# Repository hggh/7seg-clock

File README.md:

# seven segment clock with ambilight

 * 58x WS2812b 
 * ESP32
 * 74AHC125
 * XC6220 3.0V

To control the WS2812b LEDs the clock controller from wood clock light is used: https://github.com/hggh/wood-clock-light/tree/master/pcb/esp32-clock-base

### the base pcb for all ws2812b

### ESP32 to control all LEDs

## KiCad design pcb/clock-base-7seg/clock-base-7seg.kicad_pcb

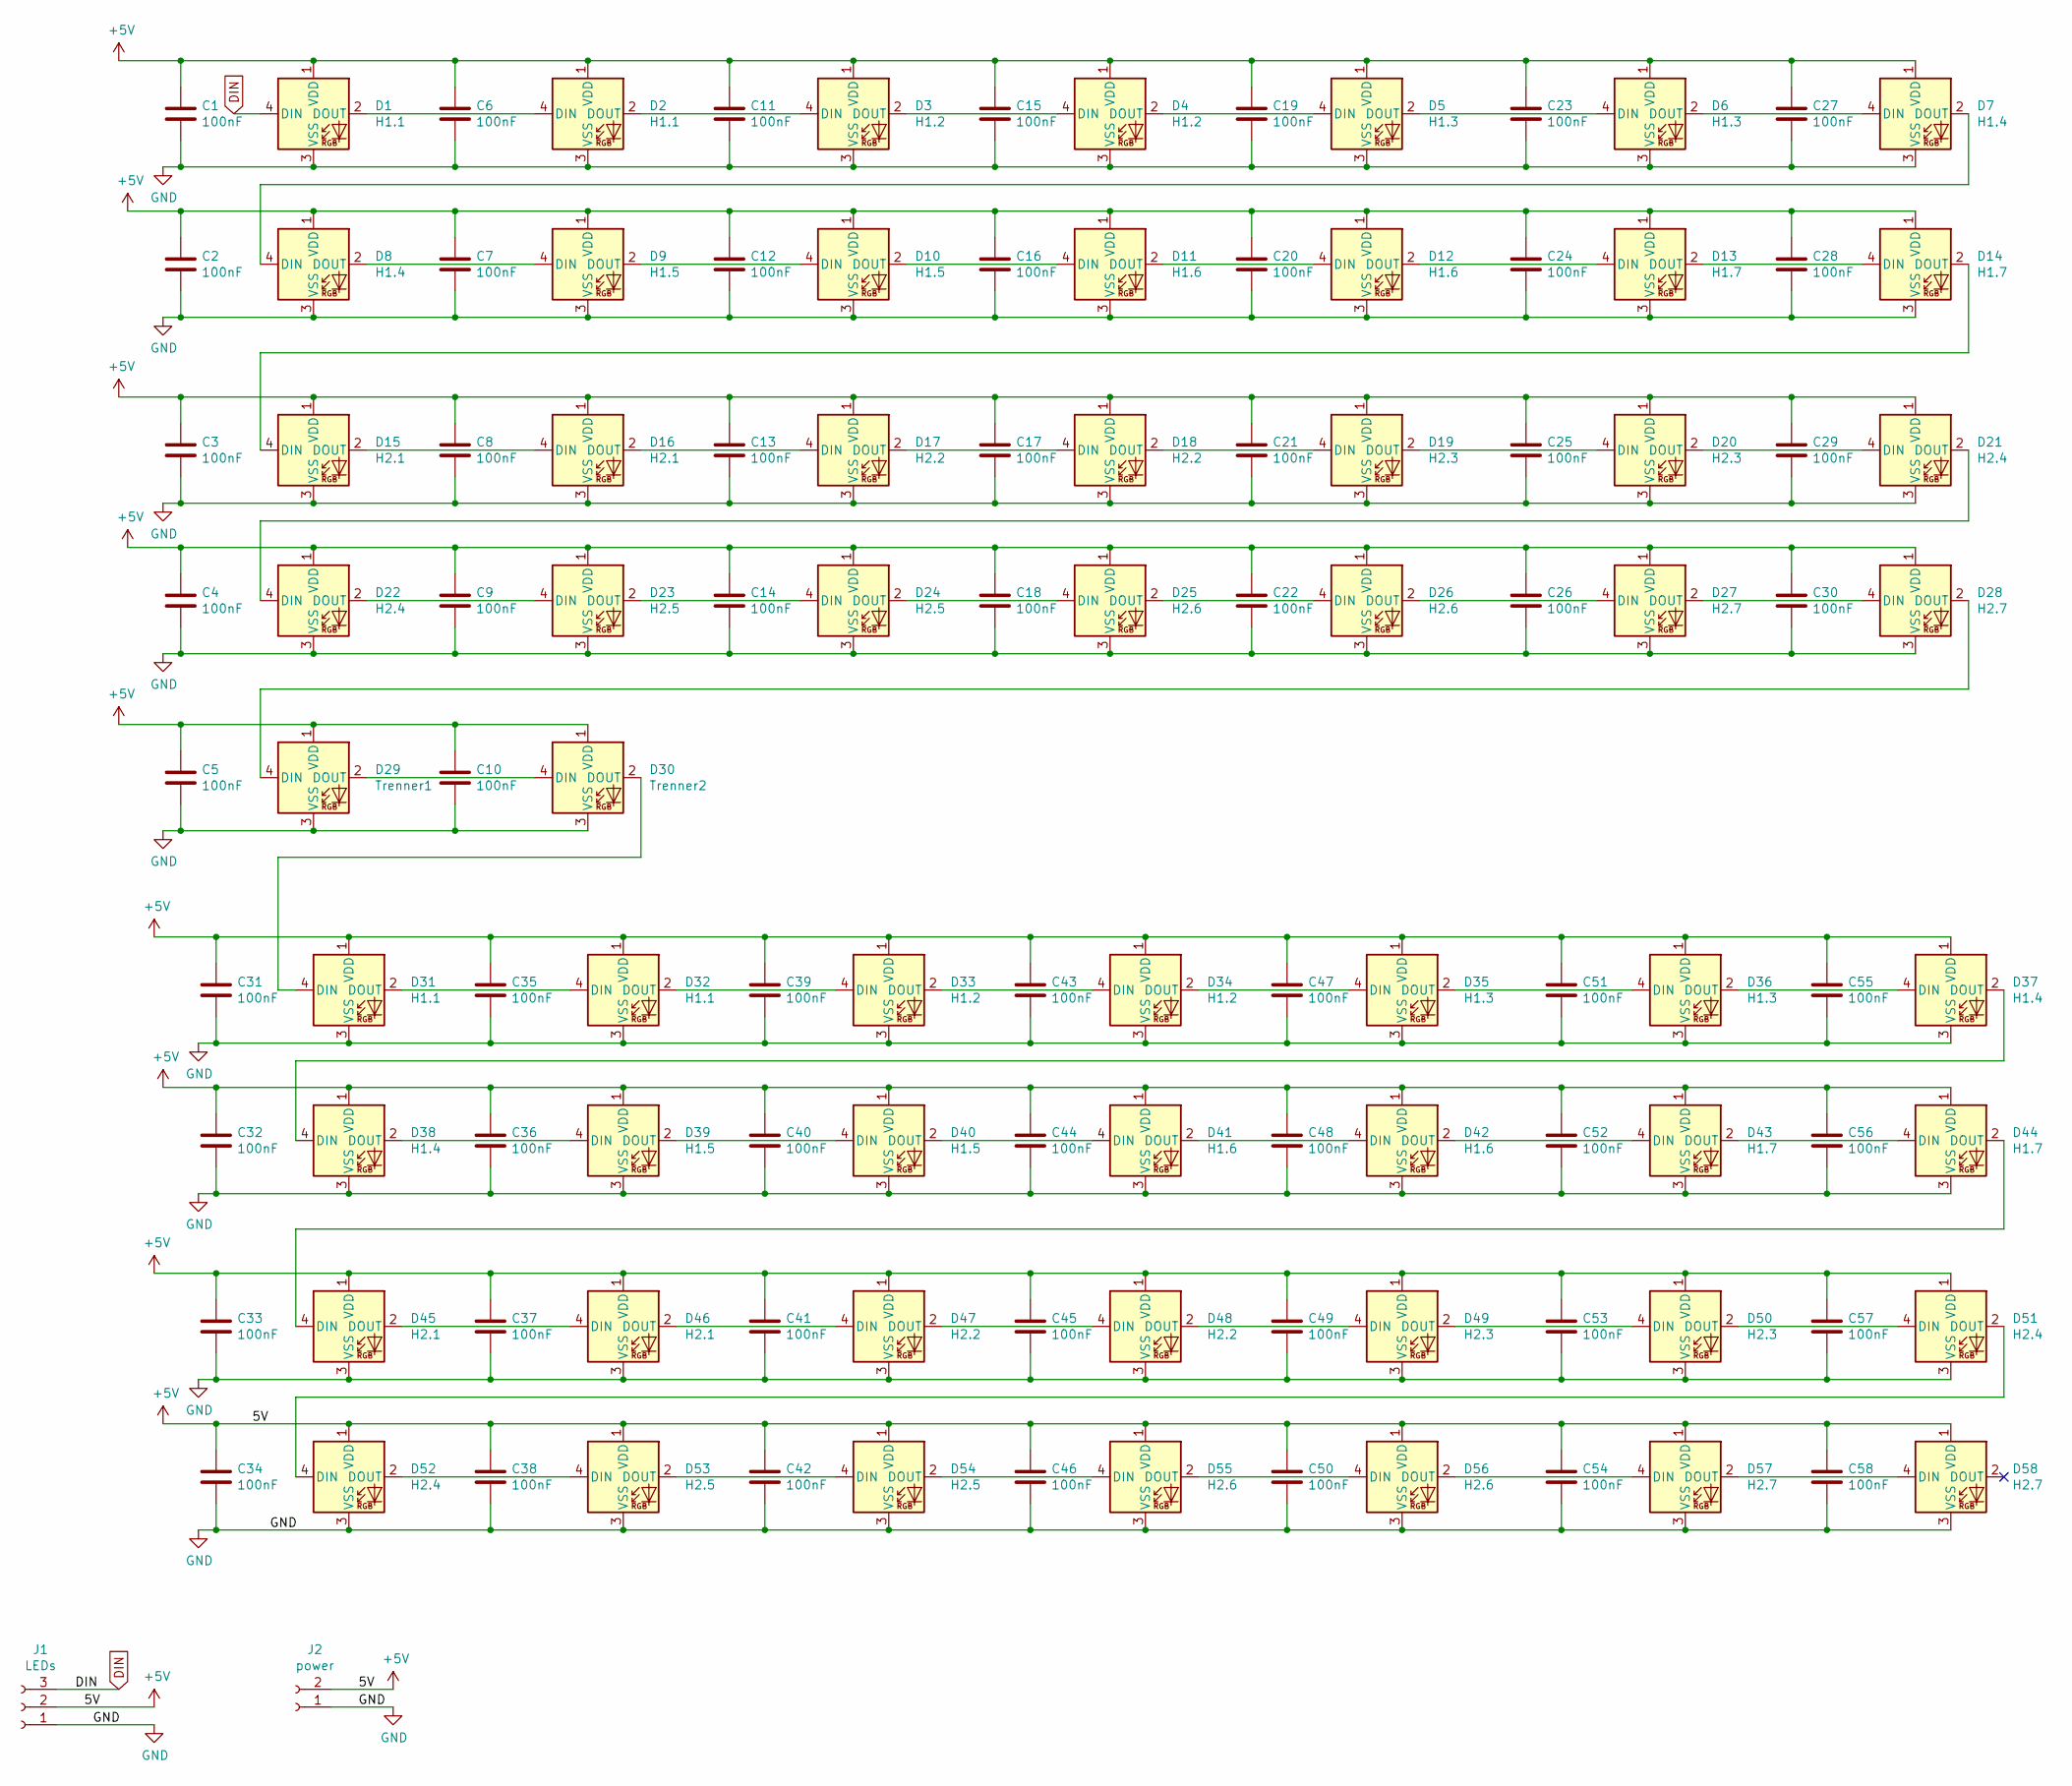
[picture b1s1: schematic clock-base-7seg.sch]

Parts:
C1, C2, C3, C4, C5, C6, C7, C8, C9, C10, C11, C12, C13, C14, C15, C16, C17, C18, C19, C20, C21, C22, C23, C24, C25, C26, C27, C28, C29, C30, C31, C32, C33, C34, C35, C36, C37, C38, C39, C40, C41, C42, C43, C44, C45, C46, C47, C48, C49, C50, C51, C52, C53, C54, C55, C56, C57, C58: 100nF; C_0805_2012Metric_Pad1.18x1.45mm_HandSolder
D1, D2, D31, D32: H1.1; LED_WS2812B_PLCC4_5.0x5.0mm_P3.2mm
D3, D4, D33, D34: H1.2; LED_WS2812B_PLCC4_5.0x5.0mm_P3.2mm
D5, D6, D35, D36: H1.3; LED_WS2812B_PLCC4_5.0x5.0mm_P3.2mm
D7, D8, D37, D38: H1.4; LED_WS2812B_PLCC4_5.0x5.0mm_P3.2mm
D9, D10, D39, D40: H1.5; LED_WS2812B_PLCC4_5.0x5.0mm_P3.2mm
D11, D12, D41, D42: H1.6; LED_WS2812B_PLCC4_5.0x5.0mm_P3.2mm
D13, D14, D43, D44: H1.7; LED_WS2812B_PLCC4_5.0x5.0mm_P3.2mm
D15, D16, D45, D46: H2.1; LED_WS2812B_PLCC4_5.0x5.0mm_P3.2mm
D17, D18, D47, D48: H2.2; LED_WS2812B_PLCC4_5.0x5.0mm_P3.2mm
D19, D20, D49, D50: H2.3; LED_WS2812B_PLCC4_5.0x5.0mm_P3.2mm
D21, D22, D51, D52: H2.4; LED_WS2812B_PLCC4_5.0x5.0mm_P3.2mm
D23, D24, D53, D54: H2.5; LED_WS2812B_PLCC4_5.0x5.0mm_P3.2mm
D25, D26, D55, D56: H2.6; LED_WS2812B_PLCC4_5.0x5.0mm_P3.2mm
D27, D28, D57, D58: H2.7; LED_WS2812B_PLCC4_5.0x5.0mm_P3.2mm
D29: Trenner1; LED_WS2812B_PLCC4_5.0x5.0mm_P3.2mm
D30: Trenner2; LED_WS2812B_PLCC4_5.0x5.0mm_P3.2mm
J1: LEDs; PinHeader_1x03_P2.54mm_Vertical
J2: power; PinHeader_1x02_P2.54mm_Vertical

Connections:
+5V: C1.1, C2.1, C3.1, C4.1, C5.1, C6.1, C7.1, C8.1, C9.1, C10.1, C11.1, C12.1, C13.1, C14.1, C15.1, C16.1, C17.1, C18.1, C19.1, C20.1, C21.1, C22.1, C23.1, C24.1, C25.1, C26.1, C27.1, C28.1, C29.1, C30.1, C31.1, C32.1, C33.1, C34.1, C35.1, C36.1, C37.1, C38.1, C39.1, C40.1, C41.1, C42.1, C43.1, C44.1, C45.1, C46.1, C47.1, C48.1, C49.1, C50.1, C51.1, C52.1, C53.1, C54.1, C55.1, C56.1, C57.1, C58.1, D1.1 (VDD), D2.1 (VDD), D3.1 (VDD), D4.1 (VDD), D5.1 (VDD), D6.1 (VDD), D7.1 (VDD), D8.1 (VDD), D9.1 (VDD), D10.1 (VDD), D11.1 (VDD), D12.1 (VDD), D13.1 (VDD), D14.1 (VDD), D15.1 (VDD), D16.1 (VDD), D17.1 (VDD), D18.1 (VDD), D19.1 (VDD), D20.1 (VDD), D21.1 (VDD), D22.1 (VDD), D23.1 (VDD), D24.1 (VDD), D25.1 (VDD), D26.1 (VDD), D27.1 (VDD), D28.1 (VDD), D29.1 (VDD), D30.1 (VDD), D31.1 (VDD), D32.1 (VDD), D33.1 (VDD), D34.1 (VDD), D35.1 (VDD), D36.1 (VDD), D37.1 (VDD), D38.1 (VDD), D39.1 (VDD), D40.1 (VDD), D41.1 (VDD), D42.1 (VDD), D43.1 (VDD), D44.1 (VDD), D45.1 (VDD), D46.1 (VDD), D47.1 (VDD), D48.1 (VDD), D49.1 (VDD), D50.1 (VDD), D51.1 (VDD), D52.1 (VDD), D53.1 (VDD), D54.1 (VDD), D55.1 (VDD), D56.1 (VDD), D57.1 (VDD), D58.1 (VDD), J1.2, J2.2
DIN: D1.4 (DIN), J1.3
GND: C1.2, C2.2, C3.2, C4.2, C5.2, C6.2, C7.2, C8.2, C9.2, C10.2, C11.2, C12.2, C13.2, C14.2, C15.2, C16.2, C17.2, C18.2, C19.2, C20.2, C21.2, C22.2, C23.2, C24.2, C25.2, C26.2, C27.2, C28.2, C29.2, C30.2, C31.2, C32.2, C33.2, C34.2, C35.2, C36.2, C37.2, C38.2, C39.2, C40.2, C41.2, C42.2, C43.2, C44.2, C45.2, C46.2, C47.2, C48.2, C49.2, C50.2, C51.2, C52.2, C53.2, C54.2, C55.2, C56.2, C57.2, C58.2, D1.3 (VSS), D2.3 (VSS), D3.3 (VSS), D4.3 (VSS), D5.3 (VSS), D6.3 (VSS), D7.3 (VSS), D8.3 (VSS), D9.3 (VSS), D10.3 (VSS), D11.3 (VSS), D12.3 (VSS), D13.3 (VSS), D14.3 (VSS), D15.3 (VSS), D16.3 (VSS), D17.3 (VSS), D18.3 (VSS), D19.3 (VSS), D20.3 (VSS), D21.3 (VSS), D22.3 (VSS), D23.3 (VSS), D24.3 (VSS), D25.3 (VSS), D26.3 (VSS), D27.3 (VSS), D28.3 (VSS), D29.3 (VSS), D30.3 (VSS), D31.3 (VSS), D32.3 (VSS), D33.3 (VSS), D34.3 (VSS), D35.3 (VSS), D36.3 (VSS), D37.3 (VSS), D38.3 (VSS), D39.3 (VSS), D40.3 (VSS), D41.3 (VSS), D42.3 (VSS), D43.3 (VSS), D44.3 (VSS), D45.3 (VSS), D46.3 (VSS), D47.3 (VSS), D48.3 (VSS), D49.3 (VSS), D50.3 (VSS), D51.3 (VSS), D52.3 (VSS), D53.3 (VSS), D54.3 (VSS), D55.3 (VSS), D56.3 (VSS), D57.3 (VSS), D58.3 (VSS), J1.1, J2.1
unnamed: D1.2 (DOUT), D2.4 (DIN)
unnamed: D2.2 (DOUT), D3.4 (DIN)
unnamed: D3.2 (DOUT), D4.4 (DIN)
unnamed: D4.2 (DOUT), D5.4 (DIN)
unnamed: D5.2 (DOUT), D6.4 (DIN)
unnamed: D6.2 (DOUT), D7.4 (DIN)
unnamed: D7.2 (DOUT), D8.4 (DIN)
unnamed: D8.2 (DOUT), D9.4 (DIN)
unnamed: D10.2 (DOUT), D11.4 (DIN)
unnamed: D9.2 (DOUT), D10.4 (DIN)
unnamed: D11.2 (DOUT), D12.4 (DIN)
unnamed: D12.2 (DOUT), D13.4 (DIN)
unnamed: D13.2 (DOUT), D14.4 (DIN)
unnamed: D14.2 (DOUT), D15.4 (DIN)
unnamed: D15.2 (DOUT), D16.4 (DIN)
unnamed: D16.2 (DOUT), D17.4 (DIN)
unnamed: D17.2 (DOUT), D18.4 (DIN)
unnamed: D18.2 (DOUT), D19.4 (DIN)
unnamed: D19.2 (DOUT), D20.4 (DIN)
unnamed: D20.2 (DOUT), D21.4 (DIN)
unnamed: D21.2 (DOUT), D22.4 (DIN)
unnamed: D22.2 (DOUT), D23.4 (DIN)
unnamed: D23.2 (DOUT), D24.4 (DIN)
unnamed: D24.2 (DOUT), D25.4 (DIN)
unnamed: D25.2 (DOUT), D26.4 (DIN)
unnamed: D26.2 (DOUT), D27.4 (DIN)
unnamed: D27.2 (DOUT), D28.4 (DIN)
unnamed: D28.2 (DOUT), D29.4 (DIN)
unnamed: D29.2 (DOUT), D30.4 (DIN)
unnamed: D30.2 (DOUT), D31.4 (DIN)
unnamed: D31.2 (DOUT), D32.4 (DIN)
unnamed: D32.2 (DOUT), D33.4 (DIN)
unnamed: D33.2 (DOUT), D34.4 (DIN)
unnamed: D34.2 (DOUT), D35.4 (DIN)
unnamed: D35.2 (DOUT), D36.4 (DIN)
unnamed: D36.2 (DOUT), D37.4 (DIN)
unnamed: D37.2 (DOUT), D38.4 (DIN)
unnamed: D38.2 (DOUT), D39.4 (DIN)
unnamed: D39.2 (DOUT), D40.4 (DIN)
unnamed: D40.2 (DOUT), D41.4 (DIN)
unnamed: D41.2 (DOUT), D42.4 (DIN)
unnamed: D42.2 (DOUT), D43.4 (DIN)
unnamed: D43.2 (DOUT), D44.4 (DIN)
unnamed: D44.2 (DOUT), D45.4 (DIN)
unnamed: D45.2 (DOUT), D46.4 (DIN)
unnamed: D46.2 (DOUT), D47.4 (DIN)
unnamed: D47.2 (DOUT), D48.4 (DIN)
unnamed: D48.2 (DOUT), D49.4 (DIN)
unnamed: D49.2 (DOUT), D50.4 (DIN)
unnamed: D50.2 (DOUT), D51.4 (DIN)
unnamed: D51.2 (DOUT), D52.4 (DIN)
unnamed: D52.2 (DOUT), D53.4 (DIN)
unnamed: D53.2 (DOUT), D54.4 (DIN)
unnamed: D54.2 (DOUT), D55.4 (DIN)
unnamed: D55.2 (DOUT), D56.4 (DIN)
unnamed: D56.2 (DOUT), D57.4 (DIN)
unnamed: D57.2 (DOUT), D58.4 (DIN)

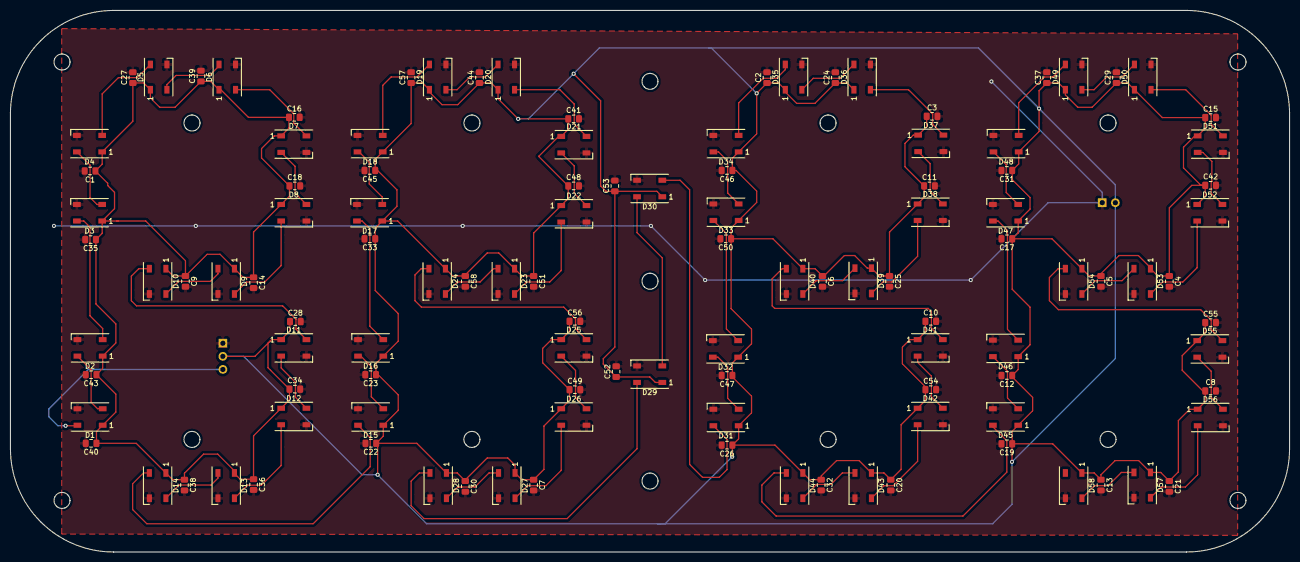
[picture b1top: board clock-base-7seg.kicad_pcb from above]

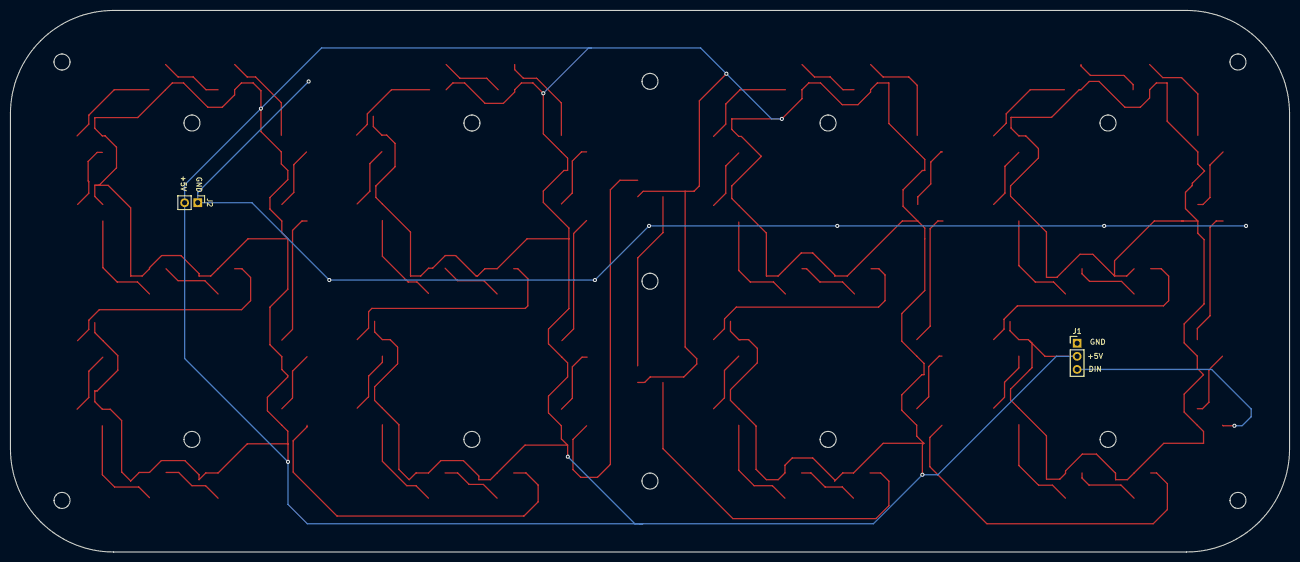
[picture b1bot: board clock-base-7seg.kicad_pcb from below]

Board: 2 copper layers, 248.0 x 105.0 mm, 118 parts (2 on the bottom side), 60 nets.

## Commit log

2021-02-22 add artwork, pcb, code
2021-02-26 update case and fabric output
2021-02-27 update final prod data
2021-02-27 fix wrong spacing
2021-02-27 work on the clock code; wifi reset, using wifi manager and Bounce for a Reset Button
2021-03-04 update pcb
2021-03-05 add usb holder
2021-03-11 add spacing
2021-04-03 bigger spacing
2021-04-03 finalize pcb
2021-04-03 add washer
2021-04-29 removed old pcb
2021-05-07 spacing for back over
2021-05-10 add stand
2021-05-10 Update code for 7seg display
2021-05-13 add ambilight
2021-05-13 add pic
2021-05-13 add pics
2021-05-13 reset variable again
2021-05-14 pin 34 has no pullup
2021-05-16 not the corect size
2021-05-21 moved to extra file
2021-05-25 update wall
2021-06-03 add holder to stick wall to frame
2021-06-03 no screws just glue the black plexiglas wall
2022-01-04 update stand to more robust version
2022-04-03 add pcb holder, add bottom part, update to webserver with html file
2022-04-05 add sleep timer start
